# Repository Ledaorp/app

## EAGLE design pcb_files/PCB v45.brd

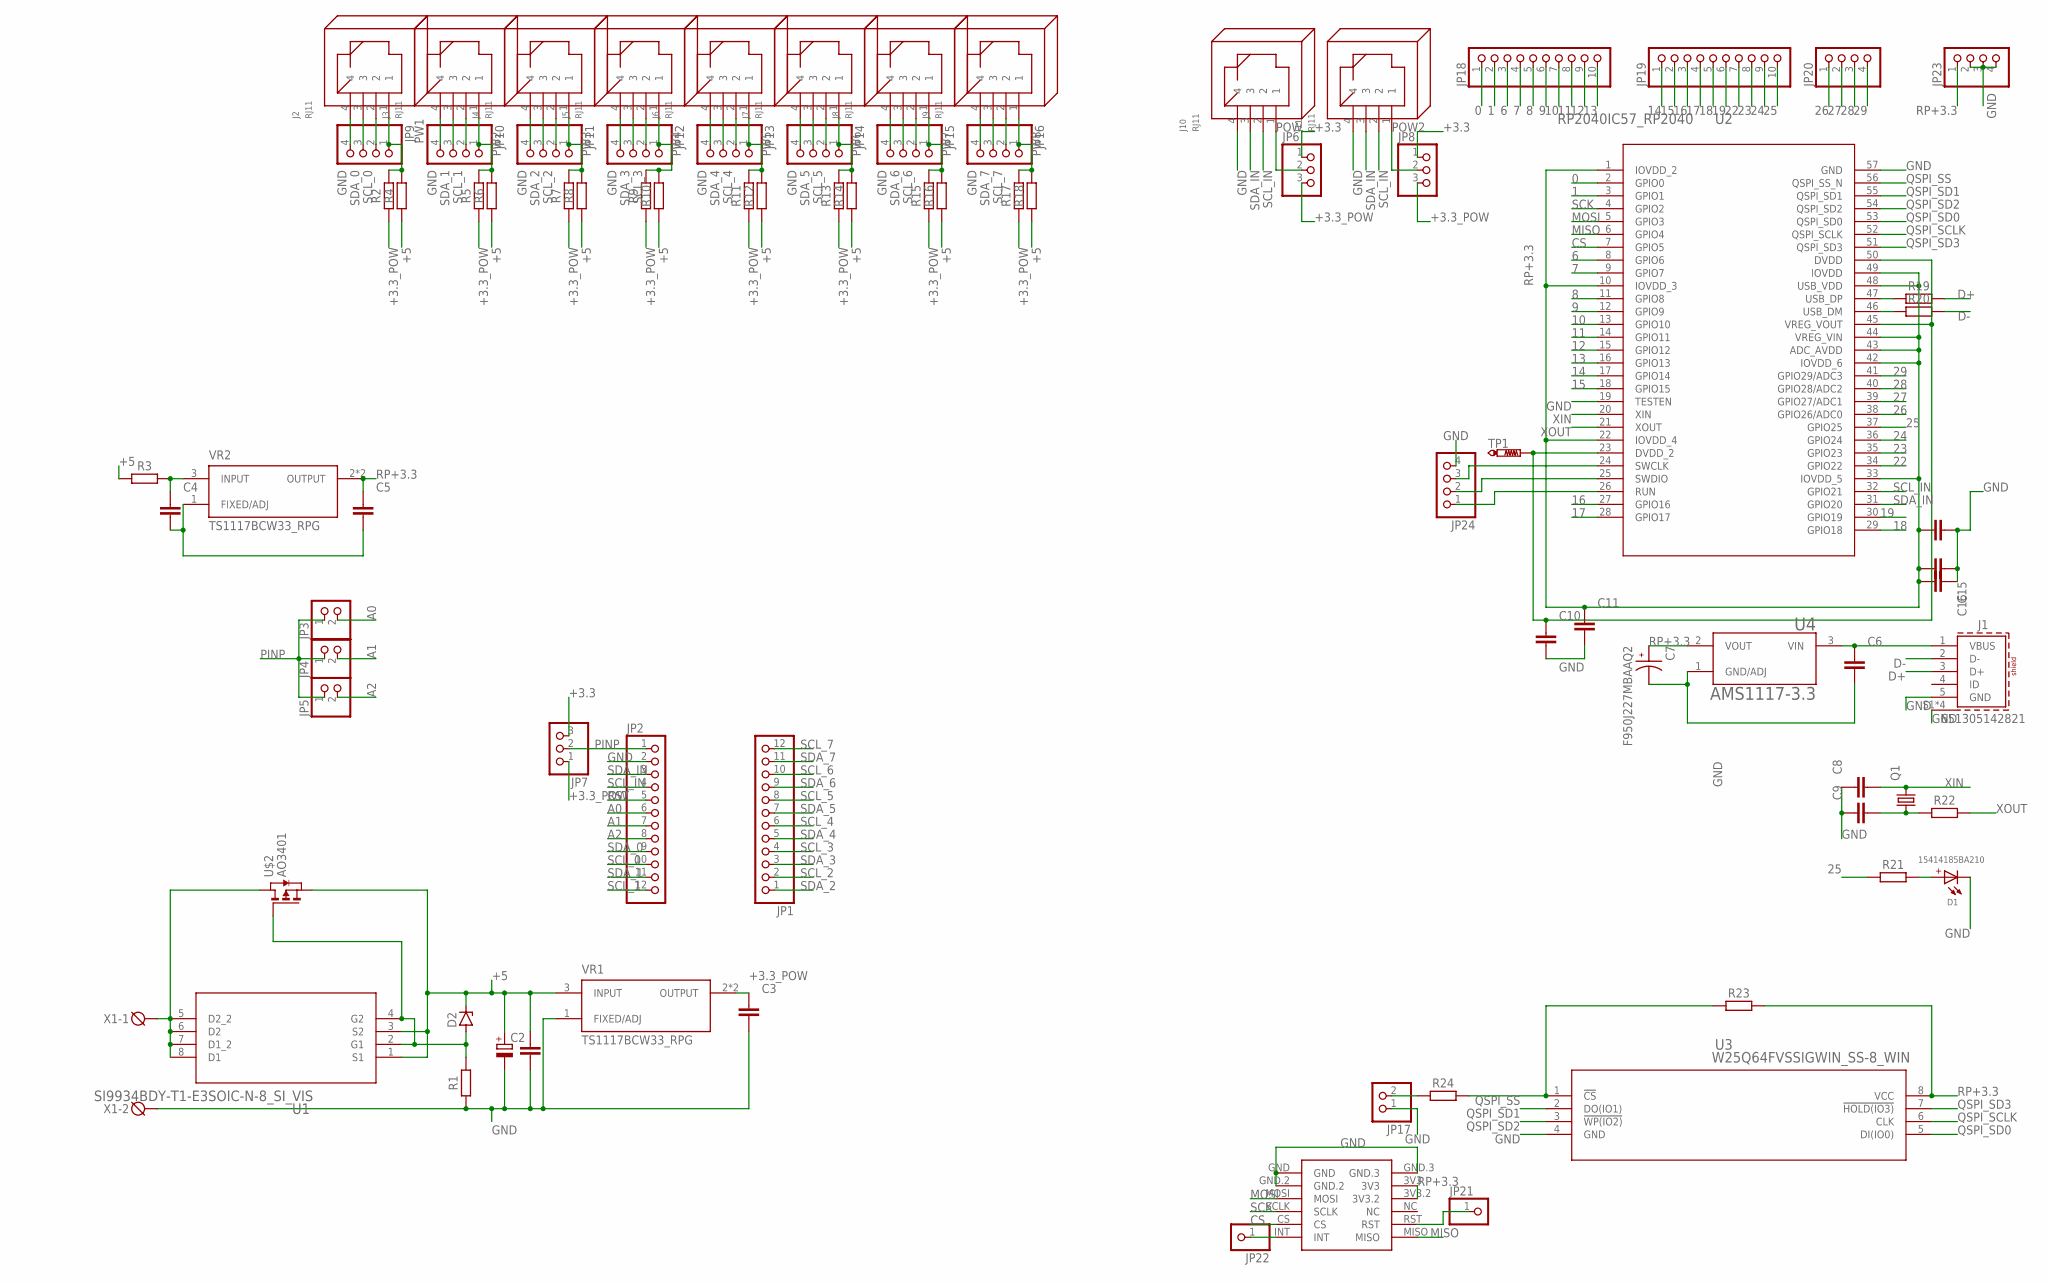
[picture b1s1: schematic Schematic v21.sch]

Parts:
C1, C3, C4, C5, C6, C8, C9, C10, C11, C12, C15, C16: C_CHIP-0805(2012-METRIC); CAPC2012X110
C2: C-POL_RADIAL-11MM-DIA; CAPPRD508W65D1000H1100B
C7: F950J227MBAAQ2; CAPCP3528X200N
D1: 15414185BA210; WL-SITW_3528
D2: ZENER-DIODESOD80C; SOD80C
J1: 651305142821
J2, J3, J4, J5, J6, J7, J8, J9, J10, J11: RJ11
JP1, JP2: PINHD-1X12; 1X12
JP3, JP4, JP5, JP17: PINHD-1X2; 1X02
JP6, JP7, JP8: PINHD-1X3; 1X03
JP9, JP10, JP11, JP12, JP13, JP14, JP15, JP16, JP20, JP23, JP24: PINHD-1X4; 1X04
JP18, JP19: PINHD-1X10; 1X10
JP21, JP22: PINHD-1X1; 1X01
Q1: KX-9A; 5.0X3.2_KX-9A
R1: R_AXIAL-7.2MM-PITCH; RESAD724W46L381D178B
R2, R4, R5, R6, R7, R8, R9, R10, R11, R12, R13, R14, R15, R16, R17, R18, R19, R20: R_CHIP-0805(2012-METRIC); RESC2012X65
R3, R21, R22, R23, R24: R_CHIP-1206(3216-METRIC); RESC3216X70
TP1: PTR1B1,27; B1,27
U1: SI9934BDY-T1-E3SOIC-N-8_SI_VIS; SOIC-N-8_SI_VIS
U2: RP2040IC57_RP2040; IC57_RP2040
U3: W25Q64FVSSIGWIN_SS-8_WIN; WIN_SS-8_WIN
U4: AMS1117-3.3; SOT229P700X180-4N
U$1: MINI_W5500
U$2: AO3401; SOT23
VR1, VR2: TS1117BCW33_RPG; VREG_TS1117BCW33_RPG
X1: DG3XX-02-3.5; DG350-3.5-02P

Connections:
0: JP18.1, U2.2 (GPIO0)
1: JP18.2, U2.3 (GPIO1)
6: JP18.3, U2.8 (GPIO6)
7: JP18.4, U2.9 (GPIO7)
8: JP18.5, U2.11 (GPIO8)
9: JP18.6, U2.12 (GPIO9)
10: JP18.7, U2.13 (GPIO10)
11: JP18.8, U2.14 (GPIO11)
12: JP18.9, U2.15 (GPIO12)
13: JP18.10, U2.16 (GPIO13)
14: JP19.1, U2.17 (GPIO14)
15: JP19.2, U2.18 (GPIO15)
16: JP19.3, U2.27 (GPIO16)
17: JP19.4, U2.28 (GPIO17)
18: JP19.5, U2.29 (GPIO18)
19: JP19.6, U2.30 (GPIO19)
22: JP19.7, U2.34 (GPIO22)
23: JP19.8, U2.35 (GPIO23)
24: JP19.9, U2.36 (GPIO24)
25: JP19.10, R21.1, U2.37 (GPIO25)
26: JP20.1, U2.38 (GPIO26/ADC0)
27: JP20.2, U2.39 (GPIO27/ADC1)
28: JP20.3, U2.40 (GPIO28/ADC2)
29: JP20.4, U2.41 (GPIO29/ADC3)
+3.3: JP6.1, JP7.3, JP8.1
+3.3_POW: C3.1, JP6.3, JP7.1, JP8.3, R2.1, R5.1, R7.1, R9.1, R11.1, R13.1, R15.1, R17.1, VR1.2 (OUTPUT), VR1.4 (OUTPUT)
+5: C1.1, C2.1 (+), D2.C, R3.1, R4.1, R6.1, R8.1, R10.1, R12.1, R14.1, R16.1, R18.1, U1.1 (S1), U1.3 (S2), U$2.2 (S), VR1.3 (INPUT)
A0: JP2.6, JP3.2
A1: JP2.7, JP4.2
A2: JP2.8, JP5.2
CS: U2.7 (GPIO5), U$1.CS
D+: J1.3 (D+), R19.2
D-: J1.2 (D-), R20.2
GND: C1.2, C2.2 (-), C3.2, C6.2, C7.2, C8.1, C9.1, C10.2, C11.2, C12.1, C15.1, C16.1, D1.2 (-), J1.5 (GND), J1.S1 (SHIELD), J1.S2 (SHIELD), J1.S3 (SHIELD), J1.S4 (SHIELD), J2.4, J3.4, J4.4, J5.4, J6.4, J7.4, J8.4, J9.4, J10.4, J11.4, JP2.2, JP9.4, JP10.4, JP11.4, JP12.4, JP13.4, JP14.4, JP15.4, JP16.4, JP17.1, JP23.2, JP23.3, JP23.4, JP24.4, R1.1, U2.19 (TESTEN), U2.57 (GND), U3.4 (GND), U4.1 (GND/ADJ), U$1.GND, U$1.GND.2, U$1.GND.3, VR1.1 (FIXED/ADJ), X1.2
MISO: U2.6 (GPIO4), U$1.MISO
MOSI: U2.5 (GPIO3), U$1.MOSI
unnamed: R19.1, U2.47 (USB_DP)
unnamed: C4.2, C5.2, VR2.1 (FIXED/ADJ)
unnamed: D2.A, R1.2, U1.2 (G1), U1.4 (G2), U$2.1 (G)
unnamed: U1.5 (D2_2), U1.6 (D2), U1.7 (D1_2), U1.8 (D1), U$2.3 (D), X1.1
unnamed: JP24.1, U2.26 (RUN)
unnamed: C4.1, R3.2, VR2.3 (INPUT)
unnamed: JP24.2, U2.25 (SWDIO)
unnamed: JP22.1, U$1.INT
unnamed: JP21.1, U$1.RST
unnamed: JP24.3, U2.24 (SWCLK)
unnamed: D1.1 (+), R21.2
unnamed: R20.1, U2.46 (USB_DM)
unnamed: C6.1, J1.1 (VBUS), U4.3 (VIN)
unnamed: C9.2, Q1.1, R22.1
unnamed: C10.1, TP1.TP, U2.23 (DVDD_2), U2.45 (VREG_VOUT), U2.50 (DVDD)
unnamed: JP17.2, R24.1
PINP: JP2.1, JP3.1, JP4.1, JP5.1, JP7.2
POW: J10.1, JP6.2
POW2: J11.1, JP8.2
PW1: J2.1, JP9.1, R2.2, R4.2
PW2: J3.1, JP10.1, R5.2, R6.2
PW3: J4.1, JP11.1, R7.2, R8.2
PW4: J5.1, JP12.1, R9.2, R10.2
PW5: J6.1, JP13.1, R11.2, R12.2
PW6: J7.1, JP14.1, R13.2, R14.2
PW7: J8.1, JP15.1, R15.2, R16.2
PW8: J9.1, JP16.1, R17.2, R18.2
QSPI_SCLK: U2.52 (QSPI_SCLK), U3.6 (CLK)
QSPI_SD0: U2.53 (QSPI_SD0), U3.5 (DI(IO0))
QSPI_SD1: U2.55 (QSPI_SD1), U3.2 (DO(IO1))
QSPI_SD2: U2.54 (QSPI_SD2), U3.3 (!WP(IO2))
QSPI_SD3: U2.51 (QSPI_SD3), U3.7 (!HOLD(IO3))
QSPI_SS: R23.1, R24.2, U2.56 (QSPI_SS_N), U3.1 (!CS)
RP+3.3: C5.1, C7.1, C11.1, C12.2, C15.2, C16.2, JP23.1, R23.2, U2.1 (IOVDD_2), U2.10 (IOVDD_3), U2.22 (IOVDD_4), U2.33 (IOVDD_5), U2.42 (IOVDD_6), U2.43 (ADC_AVDD), U2.44 (VREG_VIN), U2.48 (USB_VDD), U2.49 (IOVDD), U3.8 (VCC), U4.2 (VOUT), U$1.3V3, U$1.3V3.2, VR2.2 (OUTPUT), VR2.4 (OUTPUT)
RST: JP2.5
SCK: U2.4 (GPIO2), U$1.SCLK
SCL_0: J2.2, JP2.10, JP9.2
SCL_1: J3.2, JP2.12, JP10.2
SCL_2: J4.2, JP1.2, JP11.2
SCL_3: J5.2, JP1.4, JP12.2
SCL_4: J6.2, JP1.6, JP13.2
SCL_5: J7.2, JP1.8, JP14.2
SCL_6: J8.2, JP1.10, JP15.2
SCL_7: J9.2, JP1.12, JP16.2
SCL_IN: J10.2, J11.2, JP2.4, U2.32 (GPIO21)
SDA_0: J2.3, JP2.9, JP9.3
SDA_1: J3.3, JP2.11, JP10.3
SDA_2: J4.3, JP1.1, JP11.3
SDA_3: J5.3, JP1.3, JP12.3
SDA_4: J6.3, JP1.5, JP13.3
SDA_5: J7.3, JP1.7, JP14.3
SDA_6: J8.3, JP1.9, JP15.3
SDA_7: J9.3, JP1.11, JP16.3
SDA_IN: J10.3, J11.3, JP2.3, U2.31 (GPIO20)
XIN: C8.2, Q1.3 (2), U2.20 (XIN)
XOUT: R22.2, U2.21 (XOUT)

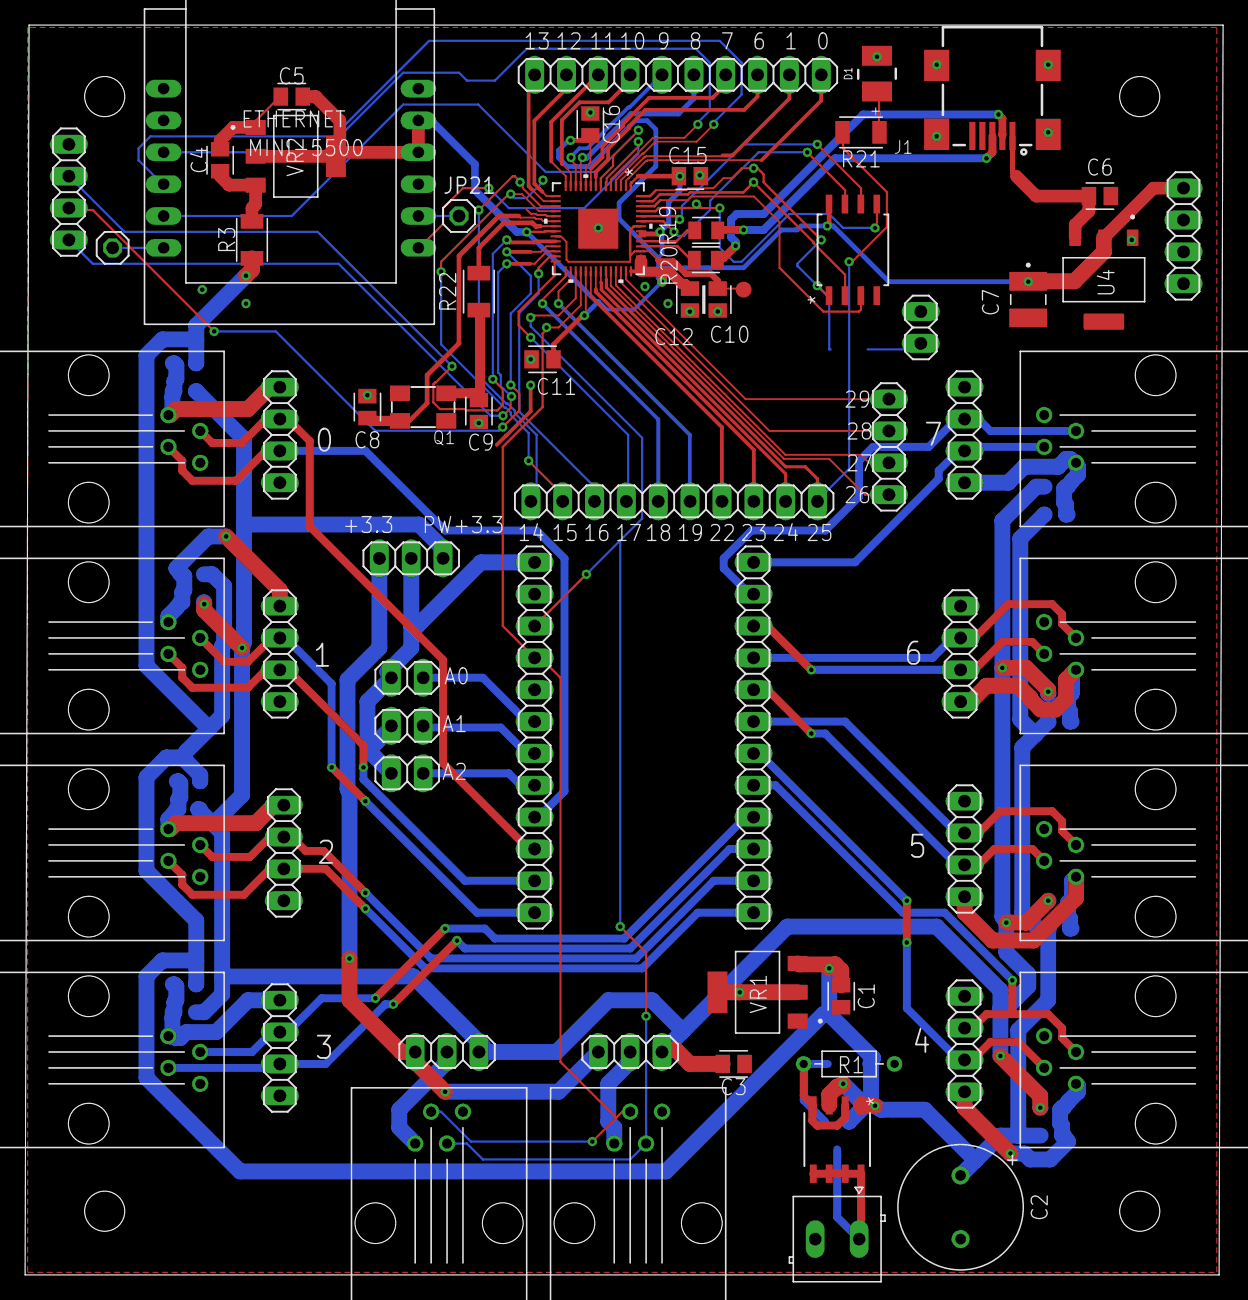
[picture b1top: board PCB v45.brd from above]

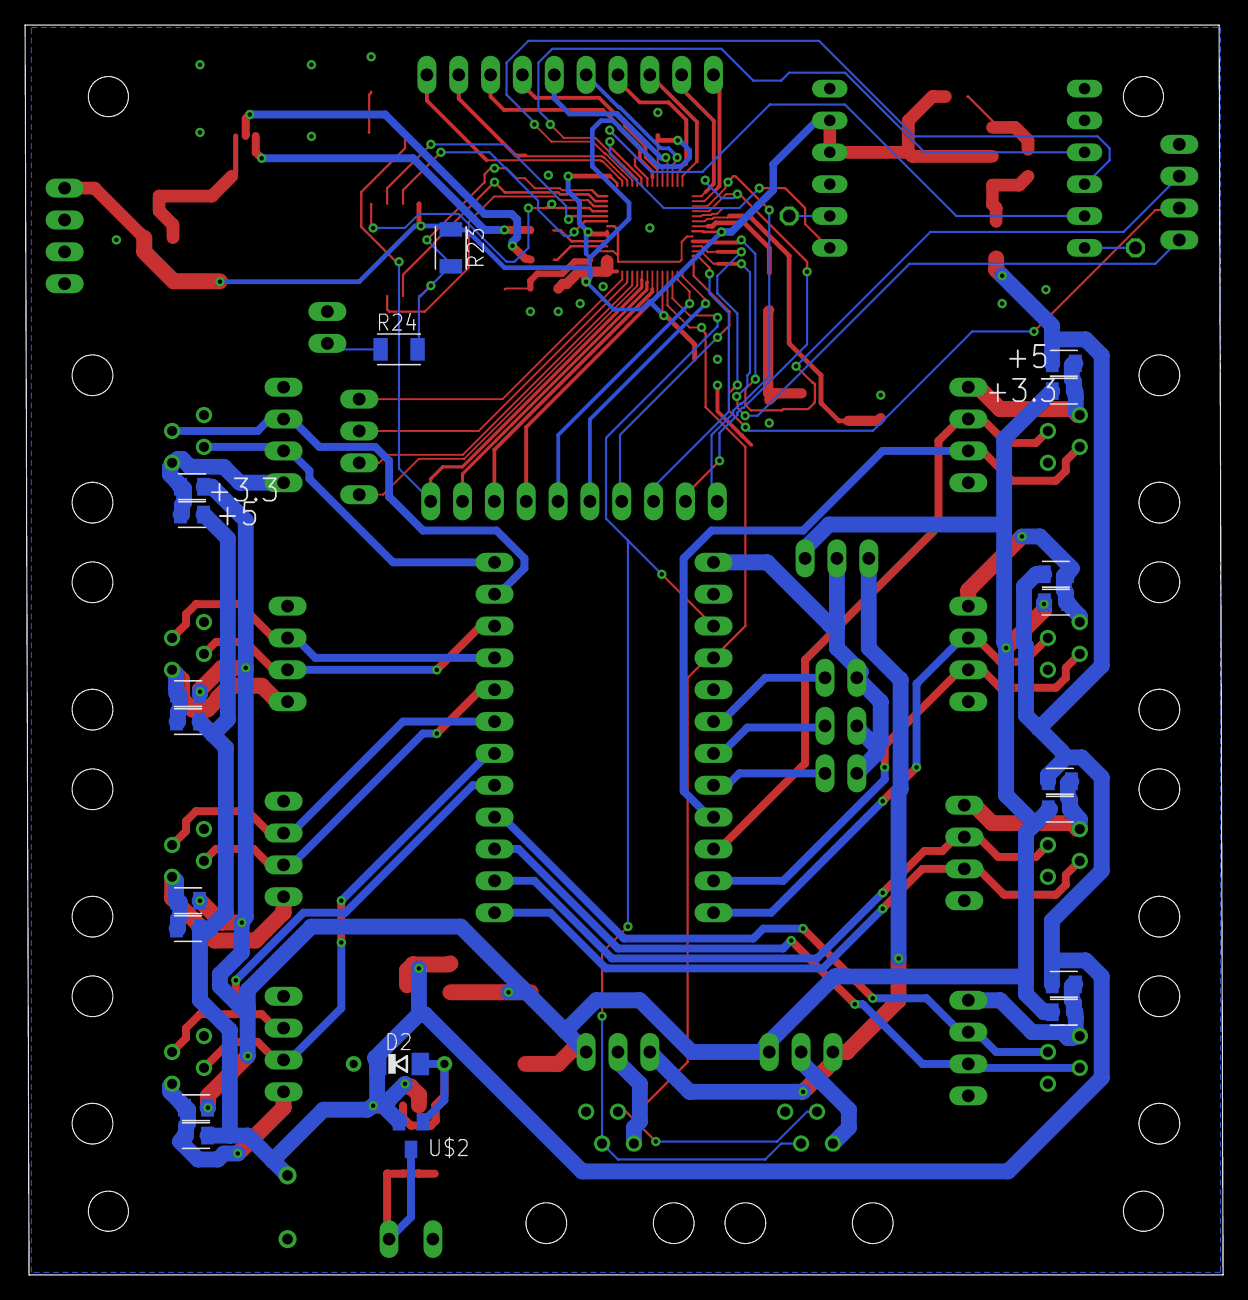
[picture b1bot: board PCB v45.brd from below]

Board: 2 copper layers, 95.5 x 99.7 mm, 86 parts (20 on the bottom side), 91 nets.

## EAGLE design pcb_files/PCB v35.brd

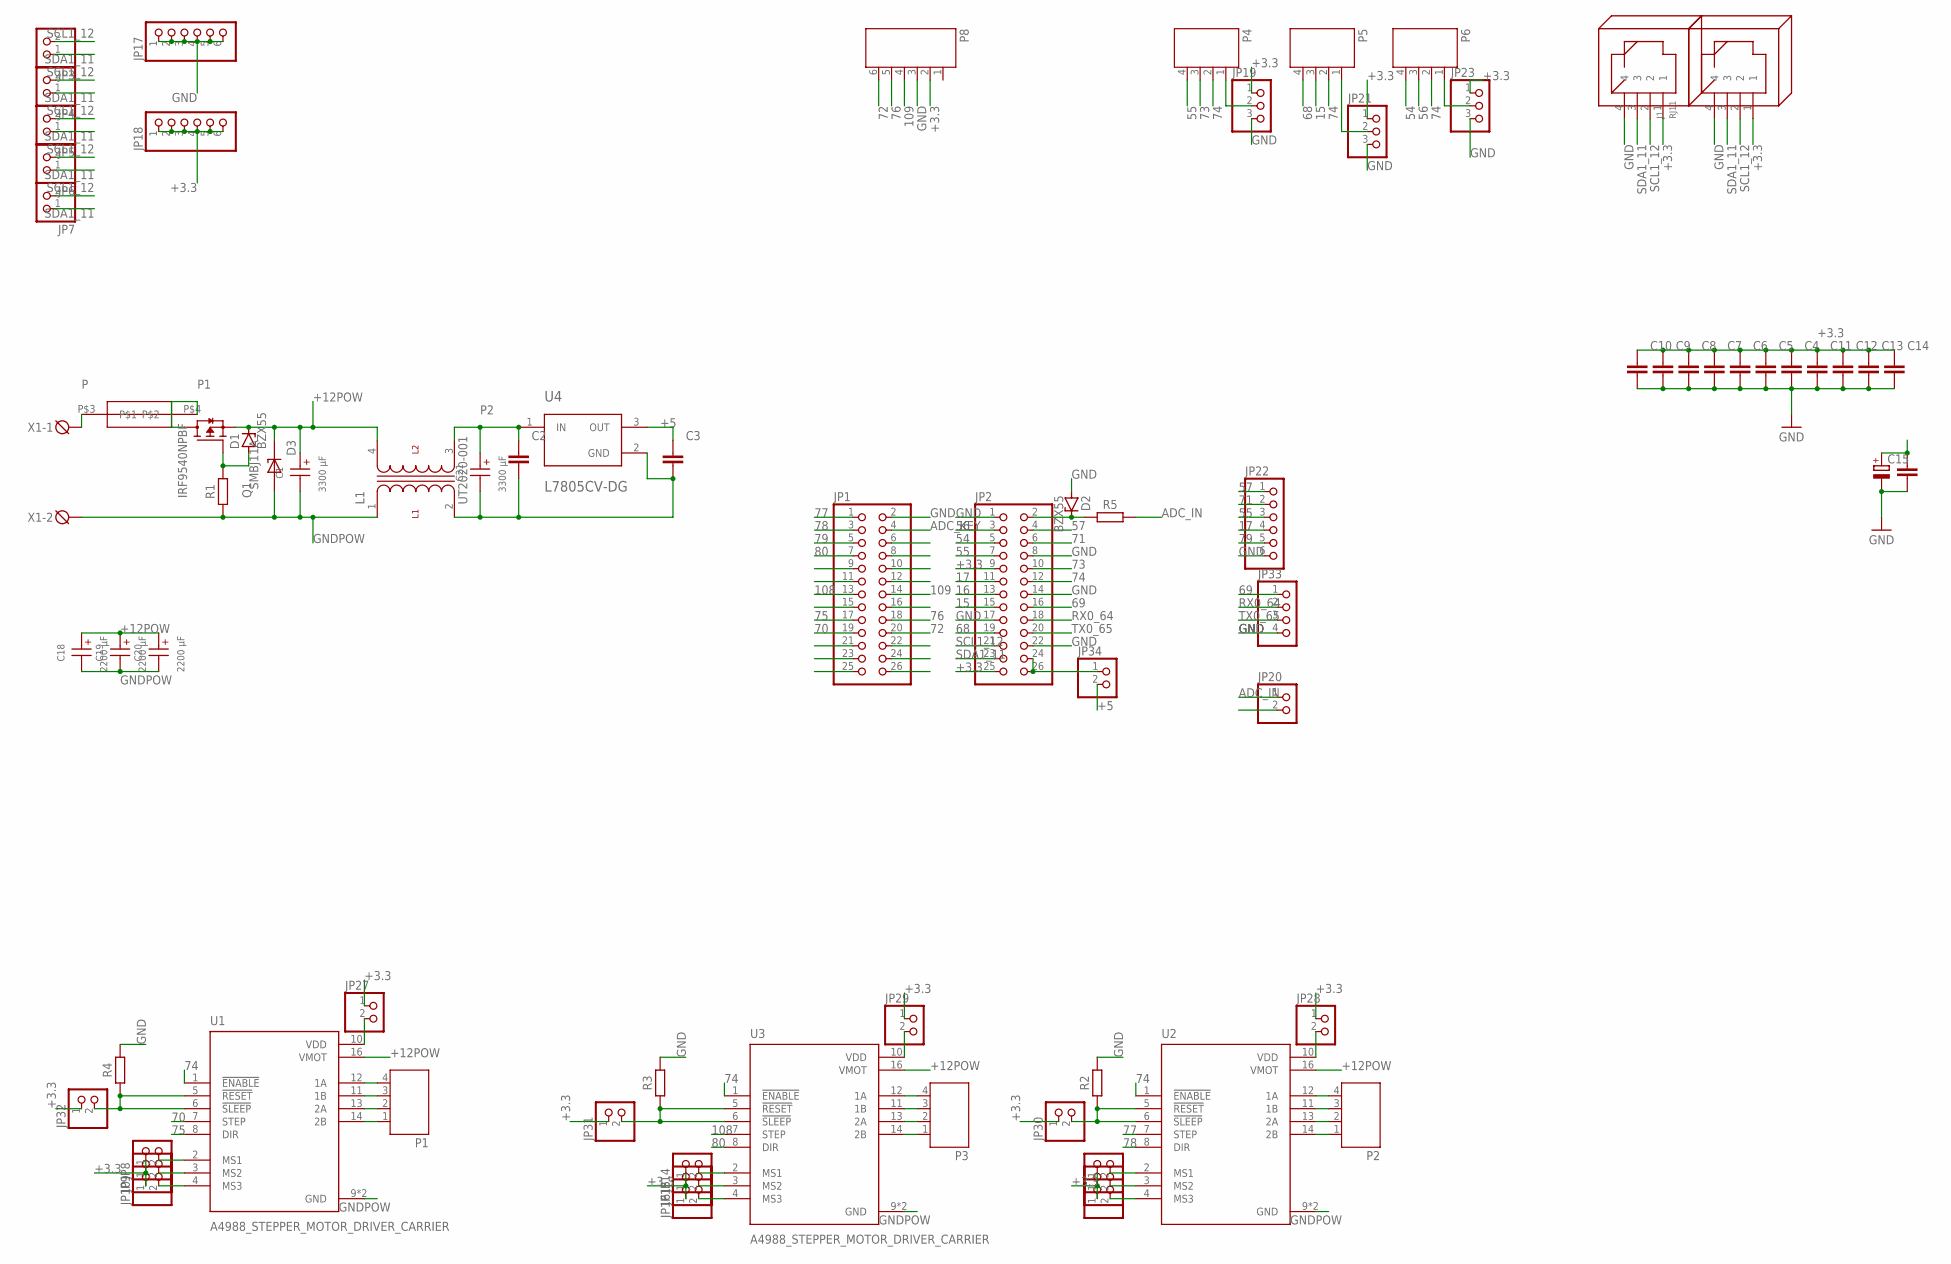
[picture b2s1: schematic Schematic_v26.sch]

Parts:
C1, C21: 3300 µF; WCAP-AT1H_13X20(DXL)
C2, C11, C12, C13, C14, C22: C_CHIP-1206(3216-METRIC); CAPC3216X135
C3, C4, C5, C6, C7, C8, C9, C10: C_CHIP-0603(1608-METRIC); CAPC1608X85
C15: C-POL_RADIAL-11MM-DIA; CAPPRD508W65D1000H1100B
C18, C19, C20: 2200 µF; WCAP-AT1H_13X20(DXL)
D1, D2: BZX55; DO35Z10
D3: SMBJ11A; DIOM4336X265N
J1, J3: RJ11
JP1, JP2: PINHD-2X13; 2X13
JP3, JP4, JP5, JP6, JP7, JP8, JP9, JP10, JP11, JP12, JP13, JP14, JP15, JP16, JP20, JP27, JP28, JP29, JP30, JP31, JP32, JP34: PINHD-1X2; 1X02
JP17, JP18, JP22: PINHD-1X6; 1X06
JP19, JP21, JP23: PINHD-1X3; 1X03
JP33: PINHD-1X4; 1X04
L1: UT2020-001; IND_UT2020-001
P1, P2, P3, P4, P5, P6: JST-PH4
P8: JST-PH6
Q1: IRF9540NPBF; TO254P1052X465X1989-3
R1: R_AXIAL-7.2MM-PITCH; RESAD724W46L381D178B
R2, R3, R4, R5: R_CHIP-1206(3216-METRIC); RESC3216X70
U1, U2, U3: A4988_STEPPER_MOTOR_DRIVER_CARRIER; MODULE_A4988_STEPPER_MOTOR_DRIVER_CARRIER
U4: L7805CV-DG; TO255P1040X460X2890-3
U$1: POJ
X1: DG3XX-02-3.5; DG350-3.5-02P

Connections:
15: JP2.15, P5.3
16: JP2.13
17: JP2.11, JP22.4
54: JP2.5, P6.4
55: JP2.7, JP22.3, P4.4
56: JP2.3, P6.3
57: JP2.4, JP22.1
68: JP2.19, P5.4
69: JP2.16, JP33.1
70: JP1.19, U1.7 (STEP)
71: JP2.6, JP22.2
72: JP1.20, P8.6
73: JP2.10, P4.3
74: JP2.12, P4.2, P5.2, P6.2, U1.1 (!ENABLE), U2.1 (!ENABLE), U3.1 (!ENABLE)
75: JP1.17, U1.8 (DIR)
76: JP1.18, P8.5
77: JP1.1, U2.7 (STEP)
78: JP1.3, U2.8 (DIR)
79: JP1.5, JP22.5
80: JP1.7, U3.8 (DIR)
108: JP1.13, U3.7 (STEP)
109: JP1.14, P8.4
+3.3: C4.1, C5.1, C6.1, C7.1, C8.1, C9.1, C10.1, C11.1, C12.1, C13.1, C14.1, J1.1, J3.1, JP2.9, JP2.25, JP8.1, JP9.1, JP10.1, JP11.1, JP12.1, JP13.1, JP14.1, JP15.1, JP16.1, JP18.1, JP18.2, JP18.3, JP18.4, JP18.5, JP18.6, JP19.1, JP21.1, JP23.1, JP27.1, JP28.1, JP29.1, JP30.1, JP31.1, JP32.1, P8.2
+5: C3.1, C15.1 (+), C22.1, JP34.2, U4.3 (OUT)
+12POW: C1.1 (+), C18.1 (+), C19.1 (+), C20.1 (+), D1.C, D3.C, L1.4, Q1.3 (S), U1.16 (VMOT), U2.16 (VMOT), U3.16 (VMOT)
ADC_IN: JP20.1, R5.2
ADC_KEY: JP1.4
GND: C2.2, C3.2, C4.2, C5.2, C6.2, C7.2, C8.2, C9.2, C10.2, C11.2, C12.2, C13.2, C14.2, C15.2 (-), C21.2 (-), C22.2, D2.A, J1.4, J3.4, JP1.2, JP2.1, JP2.8, JP2.14, JP2.17, JP2.22, JP17.1, JP17.2, JP17.3, JP17.4, JP17.5, JP17.6, JP19.3, JP20.2, JP21.3, JP22.6, JP23.3, JP33.4, L1.2, P8.3, R2.2, R3.2, R4.2, U4.2 (GND)
GNDPOW: C1.2 (-), C18.2 (-), C19.2 (-), C20.2 (-), D3.A, L1.1, R1.1, U1.9 (GND), U1.15 (GND), U2.9 (GND), U2.15 (GND), U3.9 (GND), U3.15 (GND), X1.2
unnamed: JP8.2, U1.2 (MS1)
unnamed: P1.4, U1.12 (1A)
unnamed: P1.3, U1.11 (1B)
unnamed: P1.2, U1.13 (2A)
unnamed: P1.1, U1.14 (2B)
unnamed: P2.4, U2.12 (1A)
unnamed: P2.3, U2.11 (1B)
unnamed: P2.2, U2.13 (2A)
unnamed: P2.1, U2.14 (2B)
unnamed: P3.4, U3.12 (1A)
unnamed: P3.3, U3.11 (1B)
unnamed: P3.2, U3.13 (2A)
unnamed: P3.1, U3.14 (2B)
unnamed: JP9.2, U1.3 (MS2)
unnamed: JP10.2, U1.4 (MS3)
unnamed: JP11.2, U2.2 (MS1)
unnamed: JP12.2, U2.3 (MS2)
unnamed: JP13.2, U2.4 (MS3)
unnamed: JP14.2, U3.2 (MS1)
unnamed: JP15.2, U3.3 (MS2)
unnamed: JP16.2, U3.4 (MS3)
unnamed: JP2.24, JP2.26, JP34.1
unnamed: JP30.2, R2.1, U2.5 (!RESET), U2.6 (!SLEEP)
unnamed: JP31.2, R3.1, U3.5 (!RESET), U3.6 (!SLEEP)
unnamed: D1.A, Q1.1 (G), R1.2
unnamed: JP27.2, U1.10 (VDD)
unnamed: D2.C, JP2.2, R5.1
unnamed: JP29.2, U3.10 (VDD)
unnamed: JP19.2, P4.1
unnamed: JP28.2, U2.10 (VDD)
unnamed: JP21.2, P5.1
unnamed: JP23.2, P6.1
unnamed: JP32.2, R4.1, U1.5 (!RESET), U1.6 (!SLEEP)
P: U$1.P$3, X1.1
P1: Q1.2 (D), U$1.P$4
P2: C2.1, C21.1 (+), L1.3, U4.1 (IN)
RX0_64: JP2.18, JP33.2
SCL1_12: J1.2, J3.2, JP2.21, JP3.2, JP4.2, JP5.2, JP6.2, JP7.2
SDA1_11: J1.3, J3.3, JP2.23, JP3.1, JP4.1, JP5.1, JP6.1, JP7.1
TX0_65: JP2.20, JP33.3

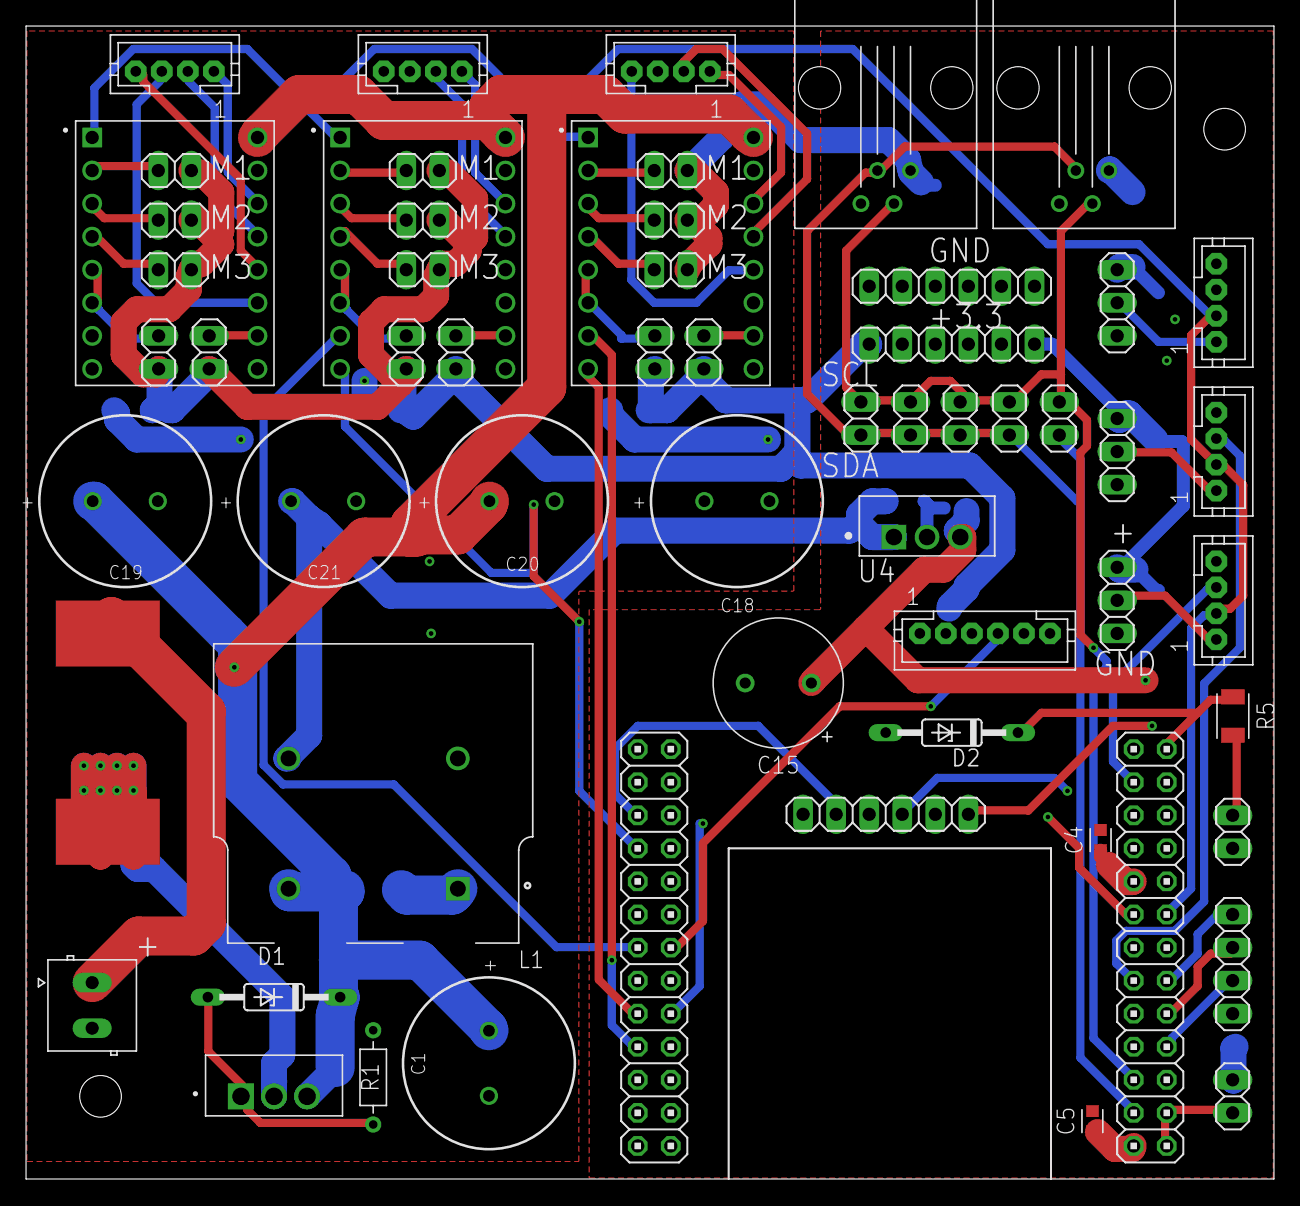
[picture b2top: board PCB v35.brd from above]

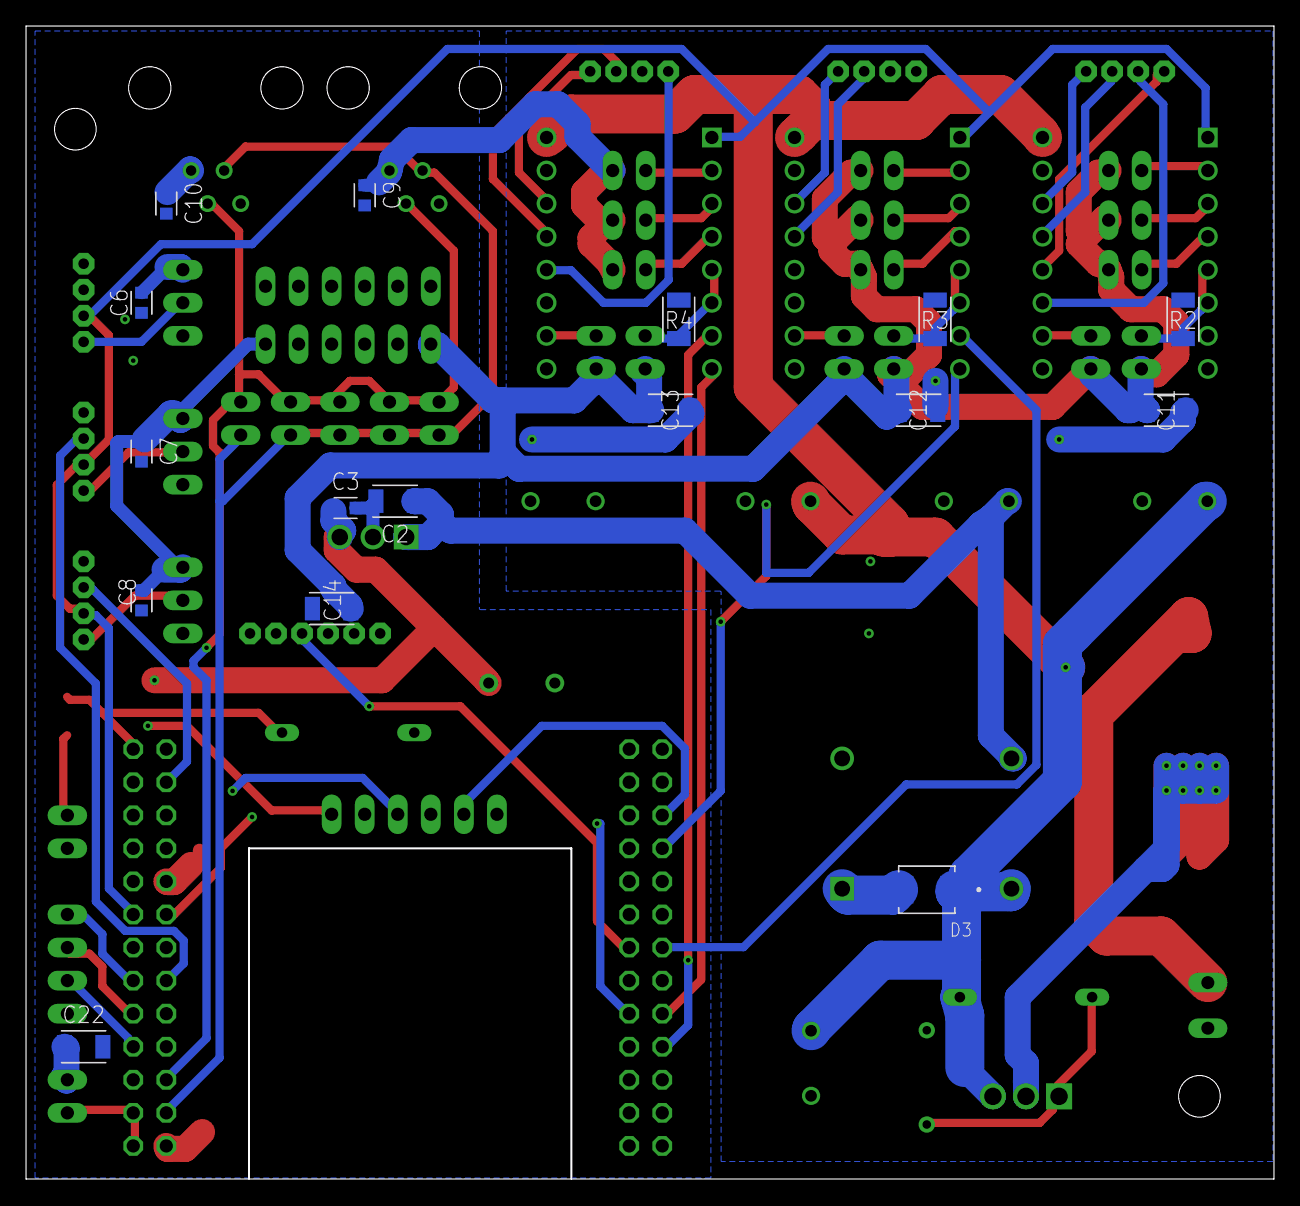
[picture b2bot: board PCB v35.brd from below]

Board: 4 copper layers, 95.9 x 88.6 mm, 76 parts (16 on the bottom side), 67 nets.

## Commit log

2025-01-13 frist
2025-02-09 adding react
2025-02-16 frontend + multiplexer
2025-02-17 small changes
2025-02-27 cleaning code + pcb files
2025-02-27 config update
2025-03-02 thredding
2025-03-14 inverse kinematics testing + updates
2025-03-18 fixing
2025-03-25 update of i2c

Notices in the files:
parts and their libraries:
Wurth_Capacitors_WCAP-AT1H: Copyright: Würth Elektronik
crystal-geyer_V1_0: Copyright: Geyer-Electronic
COPYRIGHT: Copyright (C) 2025 Ultra Librarian. All rights reserved.
